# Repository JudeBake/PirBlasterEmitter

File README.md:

# PirBlasterEmitter
Raspberry Pi IR Blaster Emitter

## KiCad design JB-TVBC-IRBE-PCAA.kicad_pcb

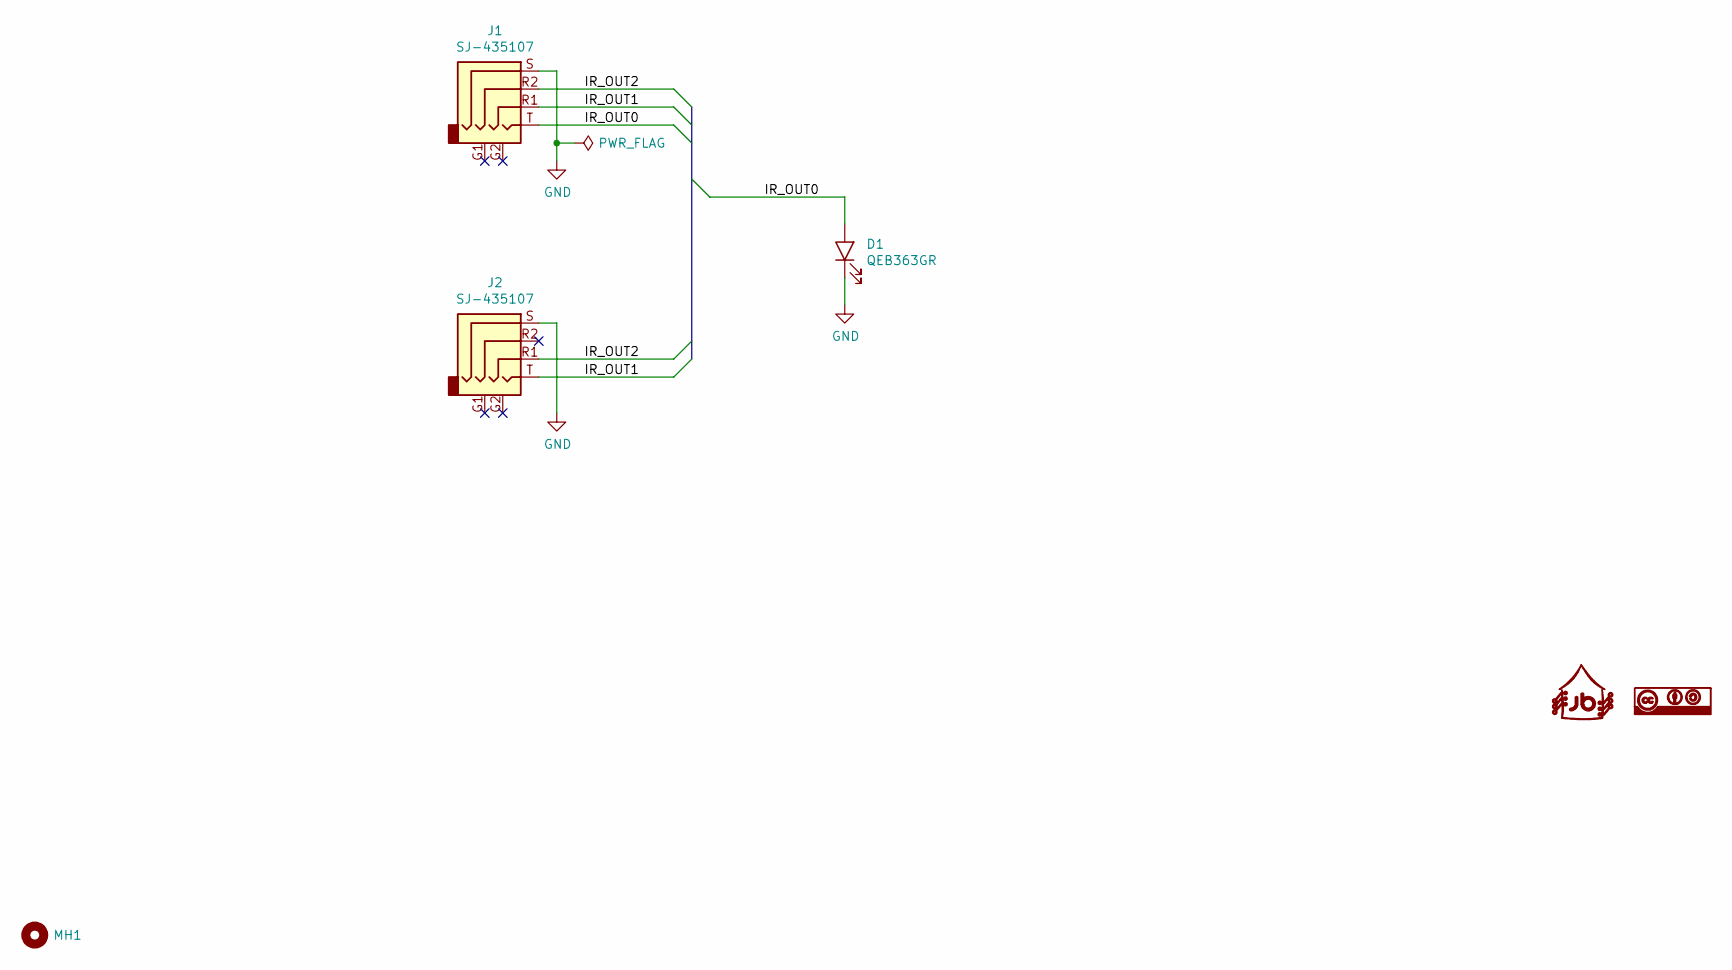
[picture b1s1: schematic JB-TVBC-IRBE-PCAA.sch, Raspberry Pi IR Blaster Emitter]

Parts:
D1: QEB363GR; Manufacturer Part Number QEB363GR; Digi-Key Part Number QEB363GRTR-ND
G1: JudeBake_Logo; JB_Logo_4MM
G2: CC-BY-SA_Logo; CC-BY-SA_4MM
J1, J2: SJ-435107; Manufacturer Part Number SJ-435107; Digi-Key Part Number CP-435107-ND
MH1: TH-NPLTD-D5.2; TH-UPLTD-D5.2

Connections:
/IR_OUT0: D1.2 (A), J1.T
/IR_OUT1: J1.R1, J2.T
/IR_OUT2: J1.R2, J2.R1
GND: D1.1 (K), J1.S, J2.S

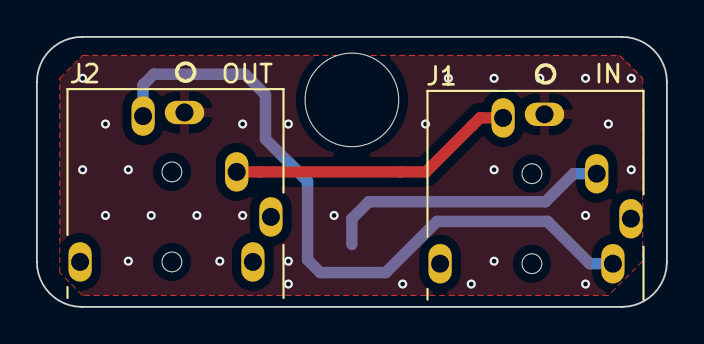
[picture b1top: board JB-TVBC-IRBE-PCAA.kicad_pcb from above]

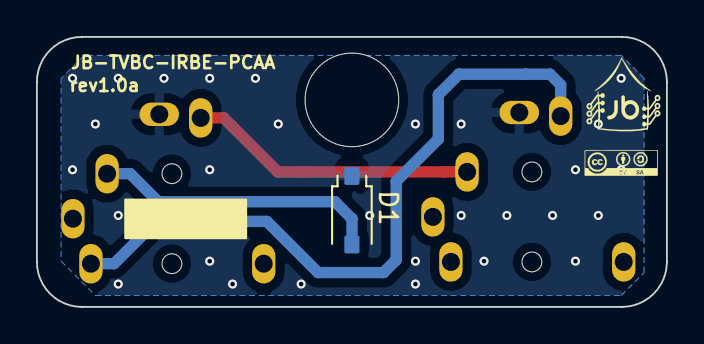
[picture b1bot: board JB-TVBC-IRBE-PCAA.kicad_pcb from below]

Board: 2 copper layers, 35.0 x 15.0 mm, 6 parts (3 on the bottom side), 4 nets.

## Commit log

2020-03-15 project creation + routing done
2020-03-15 adding interactive bom
2020-03-15 adding text on silkscreen
2020-03-15 last save
